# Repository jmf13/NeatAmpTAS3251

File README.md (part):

# NeatAmpTAS3251 — 2 × 170 W Class-D Amplifier with I²S Input, ESP32-S3 Control and DSP-Ready Design

> ⚠️ **Hobby project.** No deadlines, no warranties, no guarantees. Use at your own risk.

A stereo Class-D power amplifier built around the **Texas Instruments TAS3251**
(digital-input, 2 × 175 W into 4 Ω). It takes I²S audio directly, so there is no
analog input stage to add noise. An **ESP32-S3** configures and supervises the
amplifier over I²C (volume, EQ, faults, power sequencing), and the board is
prepared for an **ADAU1466 DSP**. A single 35 V supply feeds the power stage. Low-noise
buck + LDO rails derived from it supply everything else, and USB-C powers the digital side for
programming.

This README describes **V1.3**, the current design (KiCad 10, layout in progress).
It also explains how to bring the V1.0/V1.1 prototype boards as close to V1.3 as
possible.

---

## Contents

- [At a glance](#at-a-glance)
- [Project status](#project-status)
- [Documentation map](#documentation-map)
- [What's new in V1.3](#whats-new-in-v13)
- [Upgrading V1.0/V1.1 boards towards V1.3](#upgrading-v10v11-boards-towards-v13)
- [Building a V1.3 board](#building-a-v13-board)
- [Hardware description](#hardware-description)
  - [Power supply](#power-supply)
  - [Protection](#protection)
  - [TAS3251 amplifier](#tas3251-amplifier)
  - [ESP32-S3 controller](#esp32-s3-controller)
  - [I²S audio input](#i2s-audio-input)
- [Production details (JLCPCB)](#production-details-jlcpcb)
- [Design files and tools](#design-files-and-tools)
- [Revision history](#revision-history)
- [Next versions: ideas](#next-versions-ideas)
- [Original project and license](#original-project-and-license)

---

## At a glance

| | |
|---|---|
| Amplifier | TI TAS3251, stereo BTL, **2 × 175 W into 4 Ω** at 35 V, digital (I²S) input, built-in DSP |
| PWM frequency | 600 kHz (set by R38, selectable 600 / 500 / 450 kHz) |
| Output filter | 10 µH + 1.05 µF film caps per leg (f₀ ≈ 49 kHz). Footprints for MA5172-AE (THT; 7 µH MA5173-AE is the same family) and Coilcraft XGL1712 (SMD) |
| Supply | One external **35 V** supply (Mean Well UHP-500-36, trimmed). USB-C 5 V for the digital side only |
| Controller | ESP32-S3-WROOM-1U-N8R8 (Wi-Fi, 8 MB flash, 8 MB Octal PSRAM), firmware in [`tas/`](tas/README.md) |
| DSP | ADAU1466 ready: I²S connector, supply and I²C prepared |
| Protection | 5 A slow-blow fuse, reverse-polarity P-FET, 36 V TVS, pop-free power sequencing with PVDD monitoring |
| Cooling | ATS heatsink designed for TI's TAS3251EVM, bonded to board GND |
| PCB | 161.55 × 124.43 mm, 4 layers, 2 oz outer copper, JLCPCB assembled (top side) |
| Design tool | KiCad 10 (V1.3). EasyEDA Pro for V1.0–V1.2 |

<p align="center"><em>V1.2 PCB, top view (V1.3 renders will follow when the layout is finished)</em></p>

---

## Project status

| Version | Tool | State |
|---|---|---|
| V1.0 | EasyEDA Pro | 5 boards built (JLCPCB). Needs rework before use, see [Upgrading V1.0/V1.1](#upgrading-v10v11-boards-towards-v13) |
| V1.1 | EasyEDA Pro | USB-C orientation fix. Same rework as V1.0 otherwise |
| V1.2 | EasyEDA Pro | Layout done, DRC clean, **not produced**. Superseded by V1.3 |
| **V1.3** | **KiCad 10** | **Schematic done (ERC clean). PCB placement done, routing in progress.** Not yet produced |

**What's left before V1.3 can be ordered** is tracked in the review's
[open items summary](hw_review_2026-11-06.md#open-items):

- [pending actions](hw_review_2026-11-06.md#pending): routing, silkscreen, BOM, firmware, docs
- [parts to buy separately](hw_review_2026-11-06.md#purchase)
- [bottom-side parts](hw_review_2026-11-06.md#bottom-parts)
- [bench tests](hw_review_2026-11-06.md#hw-tests) for the first boards

⚠️ No revision has been validated in real operation yet. Treat the design as
experimental until the bench tests are done.

---

## Documentation map

| Document | What's in it |
|---|---|
| This README | Overview, V1.3 hardware description, building and upgrading boards |
| [hw_review_2026-11-06.md](hw_review_2026-11-06.md) | Full hardware review: every finding (P0 fixes, P1 savings, P2 improvements) with reasoning, datasheet references and status. Starts with the **open items summary** |
| [tas/README.md](tas/README.md) | ESP32-S3 firmware: ESP-IDF setup, build, debugging, firmware architecture, and the **step-by-step V1.0/V1.1 rework checklist** |
| [KiCADv10/README.md](KiCADv10/README.md) | How the KiCad 10 project was converted from EasyEDA, libraries and netlist checks |
| [Datasheets/](Datasheets/) | TAS3251, LMQ66430-Q1, TPS7A47, UHP-500, ADAU1462/1466, XU316-1024-QF60B (`C7397517.pdf`), heatsink datasheet and STEP |

---

## What's new in V1.3

V1.3 is the result of a full hardware review against the datasheets. The
most important changes are listed below. Each links to the detailed finding.

**Reliability and protection**

- **Reverse-polarity FET Q1 fixed.** It was mounted source-to-input on V1.0–V1.2, so it did not block a reversed supply. → [P0-6](hw_review_2026-11-06.md#p0-6)
- **F1 is now a slow-blow fuse** (0452005.MRL), sized for the 6600 µF PVDD inrush. → [P0-4](hw_review_2026-11-06.md#p0-4)
- **1 µF PVDD bypass caps right at the TAS3251 pins** (C108/C109, bottom side), as TI requires to keep output ringing below the 50 V maximum. → [V1.3-4](hw_review_2026-11-06.md#v13-4)
- **ESP32 EN pull-up** (R52 10 kΩ). EN used to float. → [P0-1](hw_review_2026-11-06.md#p0-1)
- **I²C moved off the ESP32 strapping pins** (SDA IO0 → IO47, SCL IO45 → IO21). A reset during an I²C transfer could leave the ESP32 in download mode. → [P0-2](hw_review_2026-11-06.md#p0-2)
- **C1 (feed-forward cap on the 13.2 V buck) removed.** At 10 nF it was ~50× over TI's limit. → [P0-5](hw_review_2026-11-06.md#p0-5)

**Pop-free switch-on and switch-off** → [P0-7](hw_review_2026-11-06.md#p0-7)
- RESET_AMP and ENABLE_12V are now **pulled down**: the power stage stays off until the firmware has configured it.
- **PVDD sense** divider on IO8 (R53/R54/C70): the firmware sees the supply collapse at mains-off and mutes before the power stage drops out.
- R55 10 kΩ in series with the TPS7A4701 EN pin protects it when 13.2 V is absent.

**Audio quality**

- DAC supply pins get 1 µF at the pin (C61/C67) instead of 100 nF. → [V1.3-4 #2](hw_review_2026-11-06.md#v13-4)
- DAC → SPK_IN network: 0.1 % thin-film resistors (R23–R30), C0G 1 nF, coupling caps C57–C60 moved next to the SPK_IN inputs, signal chain routed as differential pairs over a reworked AGND area. → [V1.3-4 #5](hw_review_2026-11-06.md#v13-4-f5), [P1-6](hw_review_2026-11-06.md#p1-6)
- Ferrite bead + 10 µF in front of the analog 3.3 V LDO (L15, C77). → [P2-1](hw_review_2026-11-06.md#p2-1)
- PWM frequency set by a single resistor (R38) close to the TAS3251 instead of a jumper header 35 mm away. → [V1.3-4 #6](hw_review_2026-11-06.md#v13-4-f6)

**Mechanical and PCB**

- **KiCad 10** project, 4-layer JLC04162H-7628 stack-up with **2 oz outer copper** and matching design rules. → [V1.3-3](hw_review_2026-11-06.md#v13-3)
- Board **6 mm wider**: the output stage moved to the new edge.
- **Proper heatsink** (ATS-TI1OP-1099-C1-R1, made for TI's TAS3251EVM), grounded through plated mounting holes. → [V1.3-1](hw_review_2026-11-06.md#v13-1)
- 3.3 V supply connector CN5: screw terminal → JST XH 2-pin. → [V1.3-2](hw_review_2026-11-06.md#v13-2)
- Test points reduced from 30 to 15, and all useful ones are reachable with the heatsink fitted. → [V1.3-5](hw_review_2026-11-06.md#v13-5)
- H2 expansion header reduced from 2×12 to 2×7 (now CN12).
- **All connectors renamed to CN** (V1.0–V1.2 silkscreen still shows the old names):

  | V1.0–V1.2 | V1.3 | Function |
  |---|---|---|
  | U7 | CN4 | Expansion, JST XH 6-pin |
  | U10 | CN7 | DSP control (I²C, reset, selfboot), JST XH 6-pin |
  | U11 | CN8 | I²S to/from DSP board, JST XH 6-pin |
  | U14 | CN9 | ESP32 ↔ TAS3251 control jumpers, 2×4 |
  | U15 | CN10 | Power-control jumpers, 2×4 |
  | H1 | CN11 | 4-pin header |
  | H2 | CN12 | Expansion header, 2×7 |
  | H3 | CN13 | Oscillator sync (OSC_IOM/IOP) + SDOUT, 4-pin |
  | USBC1 | CN14 | USB-C |
  | — | CN6 | New: DSP board power, JST XH 4-pin |

  Text describing V1.0/V1.1 boards (rework steps in `tas/README.md`) keeps the old names on purpose.

**BOM**

- Cheaper Basic parts where the specification allows, fewer unique parts (67 → 61 LCSC part numbers). → [P1](hw_review_2026-11-06.md#p1)
- CLIP LED is now yellow (it was the same colour as FAULT).

---

## Upgrading V1.0/V1.1 boards towards V1.3

The five V1.0/V1.1 prototypes are used for firmware development and first
listening tests. Most V1.3 fixes can be retrofitted by hand. The step-by-step
instructions (with checks after each step) are in the
[V1.0/V1.1 rework checklist](tas/README.md#hardware-v10v11-rework-checklist-before-first-power-up)
in the firmware README. This table summarises what to do and how important it is.

### Must do before the first power-up

| # | V1.3 change | What to do on V1.0/V1.1 | Steps |
|---|---|---|---|
| 1 | IO35–IO37 are reserved for the Octal PSRAM (fixed in V1.2) | Remove C51, R17, R18. Bodge the status LEDs to IO8/IO9. Don't press SW2 (or move it to IO10) | [A1–A5](tas/README.md#a-rework-soldering-iron-board-unpowered) |
| 2 | EN pull-up R52 | 10 kΩ from TP9 (EN) to 3.3 V | [A6](tas/README.md#a-rework-soldering-iron-board-unpowered) |
| 3 | C1 DNP on the 13.2 V buck | Remove C1 (10 nF). TP2 must then read 13.2 V | [A7](tas/README.md#a-rework-soldering-iron-board-unpowered) |
| 4 | Shunts on U14/U15/H2/U13 | Fit all control shunts. U13: **exactly one** pair, 3-4 = 10 kΩ = 600 kHz | [B](tas/README.md#b-shunts--jumpers) |

### Must do before running at full PVDD and high power

| # | V1.3 change | What to do on V1.0/V1.1 | Steps |
|---|---|---|---|
| 5 | 1 µF PVDD bypass at pins 35/40 (C108/C109) | Solder a 1 µF 100 V X7R from the PVDD copper nearest each pin to GND, shortest loop. **Never on the pin row** | [A8](tas/README.md#a-rework-soldering-iron-board-unpowered), [review](hw_review_2026-11-06.md#v10-pvdd) |

Until then, run at reduced PVDD (20–24 V) and low volume only.

### Recommended (makes the board behave like V1.3)

| # | V1.3 change | What to do on V1.0/V1.1 | Steps |
|---|---|---|---|
| 6 | RESET_AMP / ENABLE_12V default off | 4.7 kΩ U15-8 → GND; remove R45 and add 10 kΩ U14-6 → GND | [P1](tas/README.md#optional-pop-free-rework-v13-equivalent) |
| 7 | PVDD sense | 100 kΩ / 6.8 kΩ / 100 nF divider from TP1 to U7 pin 3 (**IO4** instead of IO8) | [P2](tas/README.md#optional-pop-free-rework-v13-equivalent) |
| 8 | F1 slow-blow | Replace F1 with 0452005.MRL (same footprint) | [P3](tas/README.md#optional-pop-free-rework-v13-equivalent) |
| 9 | SW2 user button on IO10 | Cut the trace to IO35, wire SW2 to IO10, add a 10 kΩ pull-up | [SW2 on IO10](tas/README.md#optional-sw2-on-io10-v12-equivalent) |

Without 6–8 the board works, but clicks at switch-on and thumps at switch-off.
Mute before switching off the mains ([P4](tas/README.md#optional-pop-free-rework-v13-equivalent)),
and power up from a current-limited supply rather than hot-plugging a stiff 36 V one.

### Optional (audio refinements, same footprints)

These are not in the firmware README's checklist yet. They are simple part swaps on
existing pads:

| # | V1.3 change | What to do on V1.0/V1.1 |
|---|---|---|
| 10 | 1 µF at DAC_DVDD / DAC_AVDD pins (C67/C61) | Replace the 100 nF caps at U12 pins 9 and 56 with 1 µF X7R ≥ 25 V of the same size |
| 11 | Thin-film DAC network | Replace R23–R26 (499 Ω) and R27–R30 (100 kΩ) with 0.1 % thin-film parts of the same size |
| 12 | R55 10 kΩ in series with U2 EN | Low priority. Only matters if 3.3 V is present without 13.2 V (USB-C powering) |

### Not possible on V1.0/V1.1: work around instead

| V1.3 change | Workaround on V1.0/V1.1 |
|---|---|
| Q1 reverse-polarity FET orientation | **Check CN1 polarity with a meter before every connection** ([step 12a](tas/README.md#d-first-36-v-power-up)) |
| USB-C (V1.0 only, rotated) | Flash over UART ([section C](tas/README.md#c-flash-the-firmware-first-without-36-v)). No JTAG debugging on V1.0 |
| I²C off IO0/IO45 | Stays on IO0/IO45. Harmless on the N8R8 module. If a warm reset leaves the board in download mode, power-cycle it |
| Pin map (LEDs, DSP pins, ADR) | V1.0/V1.1 boards keep the V1.2 firmware pin map. V1.3 needs the new map ([open item A17](hw_review_2026-11-06.md#pending)) |
| Grounded heatsink, wider board, 2 oz design rules, AGND rework, L15 ferrite, R38 next to FREQ_ADJ | Layout changes, not retrofittable |

The remaining differences between a reworked board and V1.2/V1.3 are listed in
[Reworked V1.0/V1.1 vs V1.2](tas/README.md#reworked-v10v11-vs-v12).

---

## Building a V1.3 board

### 1. Order

- **PCB + top-side assembly at JLCPCB.** Settings in [Production details](#production-details-jlcpcb).
  On the BOM page, set the bottom-side parts to **Do Not Place** (list below).
- **Separate LCSC order** for the bottom-side parts: JLCPCB doesn't ship loose parts with a PCBA order.
- **Mouser** (or similar): output inductors and the heatsink.
- Hardware: 2 × metal M3 screws for the heatsink, thermal paste (not an insulating pad).

The full purchase list with quantities and alternatives is in the review:
[components to purchase separately](hw_review_2026-11-06.md#purchase).

### 2. Hand-fit the parts JLCPCB doesn't place

| Part(s) | What | Source |
|---|---|---|
| C108, C109, C80, C81, C20, C68 | Bottom-side capacitors, see [Bottom-side parts](#bottom-side-parts-hand-soldered) | LCSC |
| L7–L14 | Output inductors: **one per leg**, either MA5172-AE (THT) or XGL1712-103MED (SMD) | Mouser |
| Heatsink | ATS-TI1OP-1099-C1-R1 with 2 × metal M3 screws from the bottom and thermal paste | Mouser / Digi-Key |
| R39/R40, R56 | DNP by default. Fit only for multi-board sync or target mode | LCSC |

### 3. Bring up and test

Follow the bring-up order in the review's
[HW tests and measurements](hw_review_2026-11-06.md#hw-tests):

1. **Before power:** bottom parts fitted, heatsink grounded, CN1 polarity checked.
2. **Digital side first:** power from USB-C (or 5 V on H2 pin 1) and flash the firmware.
3. **First PVDD:** current-limited bench supply at 20–24 V. Check all rails on the [test points](#test-points).
4. **Full 35 V:** inrush, PSU start-up, pop/click and output overshoot measurements.
5. **Audio:** THD+N, frequency response, inductor comparison.

---

## Hardware description

### Power supply

The supply is a multi-rail design. The noisy, high-current steps use 2.2 MHz bucks,
and the sensitive rails get an LDO after the buck.

```text
                 ┌─ U1 LMQ66430 buck ─→ +13.2V ─ FB ─→ U2 TPS7A4701 LDO ─→ 12V_GVDD (TAS3251 gate drive)
35 V PSU ─ F1 ─ Q1 ─→ PVDD ─┤
   (CN1)        (D2 TVS)    ├─ U3 LMQ66430 buck ─→ 5 V ─ D5 ─┐
                 │          │                                ├─→ +5V ─┬─ U4 AP63203 buck ─→ 3.3V (digital)
                 │   USB-C VBUS ─────────────────── D3 ──────┘        └─ L15 ─ U5 TPS7A2033 LDO ─→ +3.3VA (DAC analog)
                 └─→ TAS3251 PVDD (power stage), 3 × 2200 µF bulk
```

| Rail | Voltage | Source | Feeds |
|---|---|---|---|
| PVDD | 35 V | External PSU via F1, Q1 | TAS3251 output stage, both bucks |
| +13.2V | 13.2 V | U1 LMQ66430 buck | U2 LDO input (GOOD_13.2V = U1 power-good) |
| 12V_GVDD | 12.0 V | U2 TPS7A4701 LDO | TAS3251 GVDD_A/B. Enabled by the ESP32 (ENABLE_12V) |
| +5V (**≈ 4.6 V**) | 4.4–4.8 V | U3 buck 5.02 V (via D5) or USB-C (via D3) | 3.3 V buck, analog LDO, status LEDs, I²S connector |
| 3.3V | 3.3 V | U4 AP63203 buck | ESP32-S3, TAS3251 DAC_DVDD, ADAU1466 digital |
| +3.3VA | 3.3 V | U5 TPS7A2033 LDO | TAS3251 DAC_AVDD only |

#### External PVDD supply: Mean Well UHP-500-36

The recommended supply is the **Mean Well UHP-500-36**
([datasheet](Datasheets/UHP-500-spec.pdf)).

| Parameter | UHP-500-36 | Relevance to this board |
|---|---|---|
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
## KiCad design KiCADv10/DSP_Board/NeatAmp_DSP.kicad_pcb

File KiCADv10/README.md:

# NeatAmp MainBoard – KiCad schematic generated from EasyEDA Pro netlist

Source: `Netlist_Class_D_amp_2026-11-10.enet` (EasyEDA Pro, V1.2), 233 components, 138 nets.

## Status
- **Verified:** KiCad's exported netlist matches the EasyEDA netlist exactly (138/138 nets, identical pin sets; 31 NC pins = 31 no-connect flags).
- **Faithful 1:1 copy of V1.2.** The P0 fixes from `hw_review_2026-11-06.md` are **not** applied yet. Apply them as a separate commit.
- Written in KiCad 7 file format; KiCad 10 opens it and upgrades it on save.

## How it is drawn
- 5 sheets = original EasyEDA pages (page taken from each part's EasyEDA Channel ID).
- Every pin carries a label: **global labels** for named nets (cross-sheet), **local labels** `N<page>N<id>` for EasyEDA auto-nets (`$4N1568` → `N4N1568`).
- Parts are grouped around the IC they connect to (power nets ignored for grouping); pure decoupling parts sit in a separate group.
- Symbols are generic boxes generated from the real pin numbers/names (library `NeatAmp.kicad_sym`). Swap them for nicer symbols later with *Change Symbol*; pins match by number.
- Every symbol keeps its fields: Value, Footprint, LCSC, MPN, Manufacturer, JLC Class, Datasheet, Description, original EasyEDA footprint/device name. `in_bom` follows EasyEDA "Add into BOM" (test points excluded).

## Libraries
1. `pip install easyeda2kicad`
2. `./get_lcsc_libs.sh`: fetches symbol + footprint + 3D for all 67 LCSC numbers into `libs/easyeda2kicad.*`.
3. Footprint fields point to `easyeda2kicad:<EasyEDA footprint name>`. easyeda2kicad normally names footprints the same way. Any that differ show up as missing footprints in *Update PCB from Schematic*; fix them with *Tools → Edit Symbol Fields* (filter by the `EasyEDA Footprint` column).
4. Parts without LCSC number:
   - Test points → `TestPoint:TestPoint_Pad_D1.0mm` (KiCad standard)
   - L7/L9/L11/L13 (XGL1712, SMD) → `NeatAmp_custom:IND-SMD_L17.2-W18.2` (converted from the EasyEDA footprint in `EasyEDA-Pro/libraries/TAS3251Components.elib`; no 3D model yet) and L8/L10/L12/L14 (MA5172-AE, THT) → `NeatAmp_custom:MA5172AE` (vendor KiCad footprint + `NeatAmp_custom.3dshapes/MA5172-AE.stp`). Both footprints are intentional (alternative inductors to compare); only one per leg is mounted.

## Re-check after editing
```
kicad-cli sch export netlist --format kicadxml -o new.xml NeatAmp.kicad_sch
python3 tools/cmp.py Netlist_Class_D_amp_2026-11-10.enet new.xml
```
(Expect differences only where you deliberately changed the circuit.)

## Regenerate
`python3 tools/gen.py <netlist.enet> <outdir> NeatAmp`

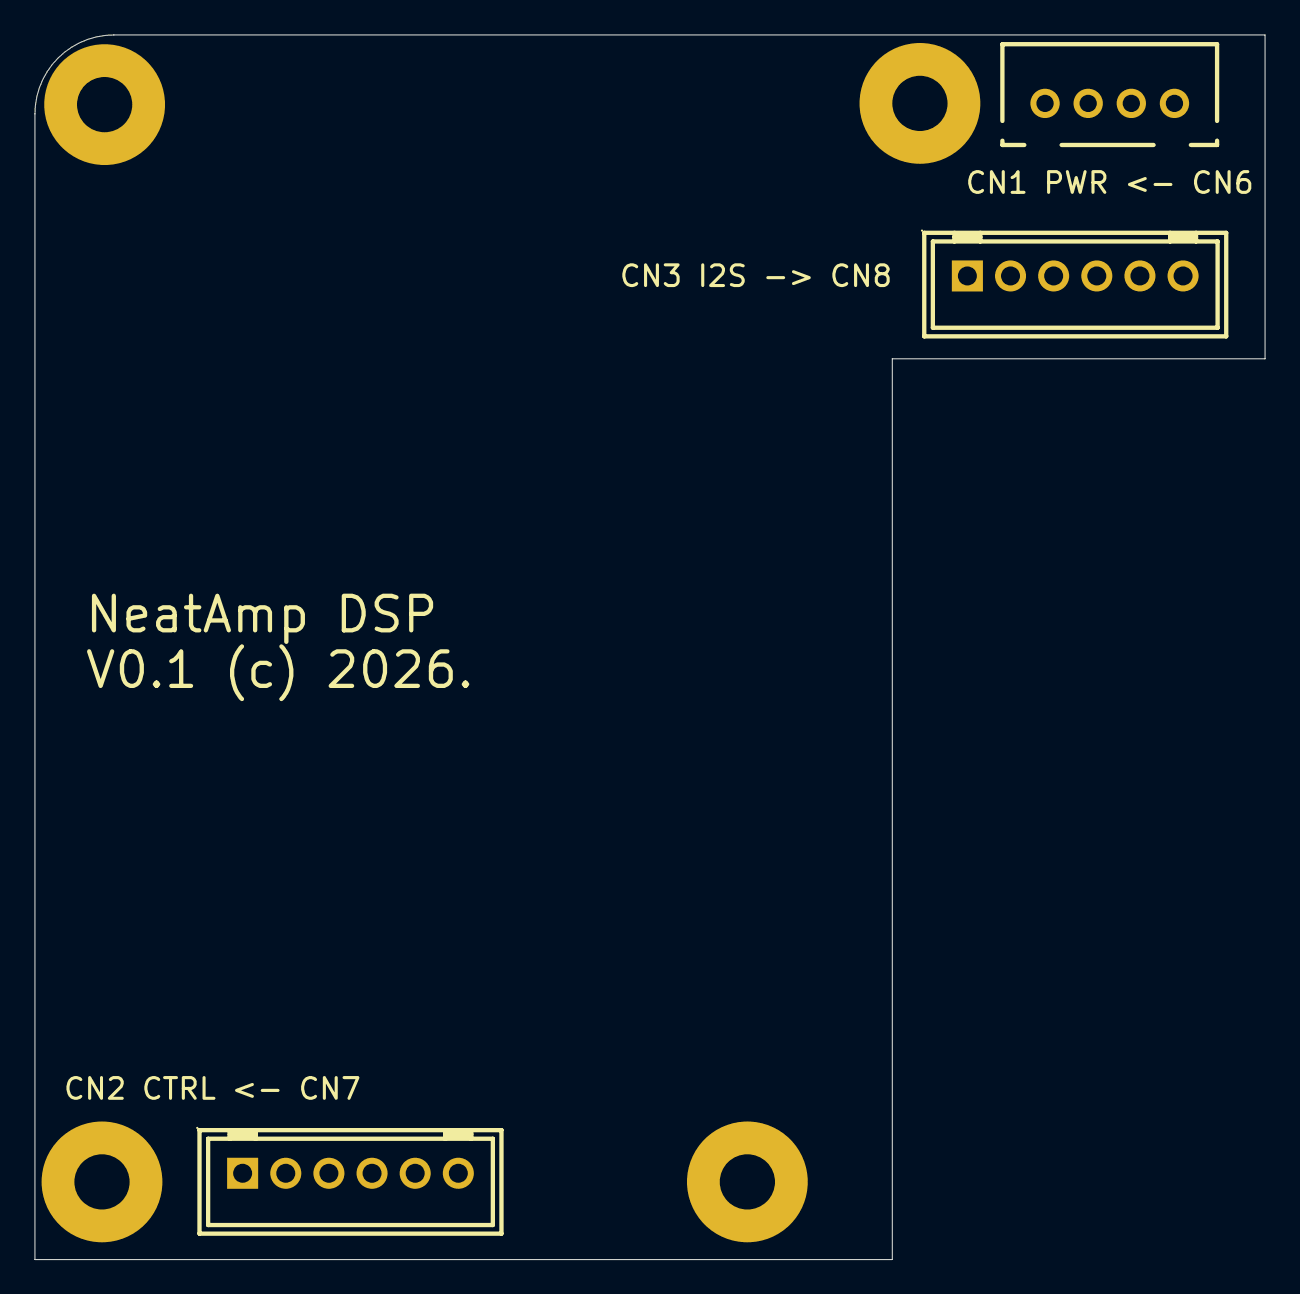
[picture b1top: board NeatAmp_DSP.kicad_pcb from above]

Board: 4 copper layers, 71.3 x 71.0 mm, 7 parts (0 on the bottom side), 2 nets, no tracks yet.

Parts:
CN1: B4B-XH-A(LF)(SN); CONN-TH_B4B-XH-A-LF-SN
CN2, CN3: B6B-XH-A(LF)(SN); CONN-TH_6P-P2.50_B6B-XH-A-LF-SN
MH1, MH2, MH3, MH4: M3; MountingHole_3.2mm_M3_Pad_7mm

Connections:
/+5V_IN: CN1.1, CN1.2
/GND: CN1.3, CN1.4, CN2.1, CN3.1

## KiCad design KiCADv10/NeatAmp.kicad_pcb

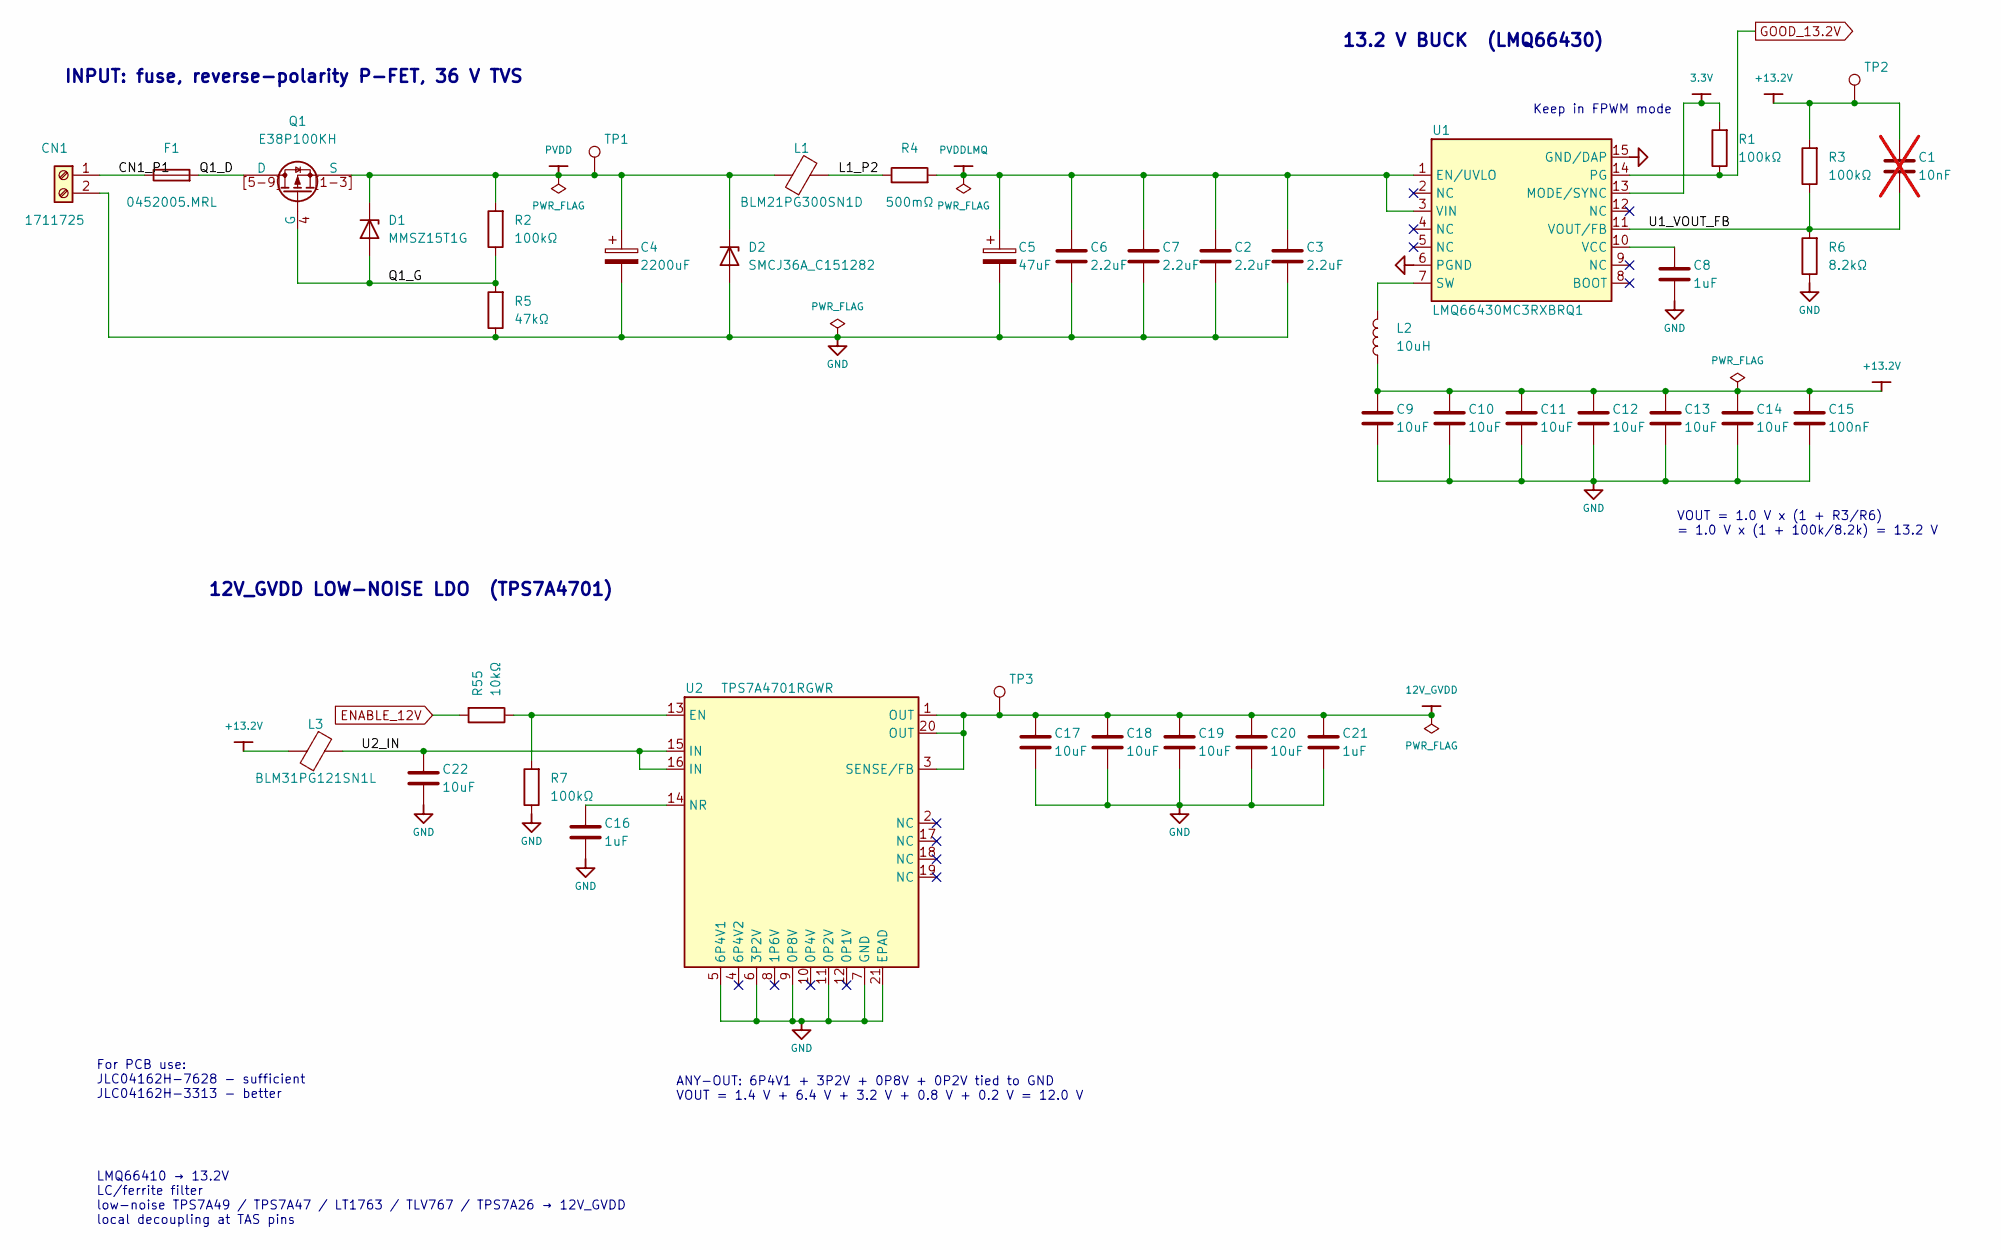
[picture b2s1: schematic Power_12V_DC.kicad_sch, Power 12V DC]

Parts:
C1: 10nF; C0402; MPN FCC0402B103K500AT; LCSC C5137480; not fitted
C2, C3, C6, C7: 2.2uF; C1206; MPN CL31B225KCHSNNE; LCSC C170101
C4: 2200uF; CAP-TH_BD18.0-P7.5-D0.8-FD; MPN NXA 63V 2200UF 18*40; LCSC C2827938
C5: 47uF; CAP-SMD_BD6.3-L6.6-W6.6-LS7.2-FD; MPN VZH470M1HTR-0607L; LCSC C2902971
C8: 1uF; C1206; MPN CL31B105KCHNNNE; LCSC C13832
C9, C10, C11, C12, C13, C14, C17, C18, C19, C20, C22: 10uF; C1210; MPN CL32B106KBJNNNE; LCSC C138687
C15: 100nF; C0402; MPN CL05B104KB54PNC; LCSC C307331
C16, C21: 1uF; C0603; MPN CL10B105KB8NQNC; LCSC C5199872
CN1: 1711725; CONN-TH_MKDS3-2-5.08; MPN 1711725; LCSC C89120
D1: MMSZ15T1G; SOD-123_L2.7-W1.6-LS3.7-RD; MPN MMSZ15T1G; LCSC C27754
D2: SMCJ36A_C151282; SMC_L7.1-W6.2-LS8.1-RD; MPN SMCJ36A; LCSC C151282
F1: 0452005.MRL; FUSE-SMD_L6.1-W2.6; MPN 0452005.MRL; LCSC C66503
L1: BLM21PG300SN1D; L0805; MPN BLM21PG300SN1D; LCSC C16903
L2: 10uH; IND-SMD_L7.1-W6.6; MPN SLO0630H100MTT; LCSC C207842
L3: BLM31PG121SN1L; L1206; MPN BLM31PG121SN1L; LCSC C85841
Q1: E38P100KH; DFN-8_L6.0-W5.0-P1.27-LS6.2-BL_VBQA2309; MPN E38P100KH; LCSC C29781155
R1, R2, R3, R7: 100kΩ; R0603; MPN 0603WAF1003T5E; LCSC C25803
R4: 500mΩ; R2512; MPN 25121WF500LT4E; LCSC C27777
R5: 47kΩ; R0603; MPN 0603WAF4702T5E; LCSC C25819
R6: 8.2kΩ; R0603; MPN FRC0603F8201TS; LCSC C2907069
R55: 10kΩ; R0603; MPN 0603WAF1002T5E; LCSC C25804
TP1, TP2, TP3: Test-Point; TestPoint_Pad_D1.0mm
U1: LMQ66430MC3RXBRQ1; VQFN-14_L2.6-W2.6-P0.50-BL; MPN LMQ66430MC3RXBRQ1; LCSC C19271903
U2: TPS7A4701RGWR; VQFN-20_L5.0-W5.0-P0.65-TL-EP; MPN TPS7A4701RGWR; LCSC C90084

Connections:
3.3V: R1.2, U1.13 (MODE/SYNC); also elsewhere on the board
12V_GVDD: C17.1, C18.1, C19.1, C20.1, C21.1, TP3.1 (1_1), U2.1 (OUT), U2.3 (SENSE/FB), U2.20 (OUT); also elsewhere on the board
+13.2V: C1.2, C9.1, C10.1, C11.1, C12.1, C13.1, C14.1, C15.2, L2.1, L3.2, R3.2, TP2.1 (1_1)
/Power 12V DC/CN1_P1: CN1.1, F1.1
/Power 12V DC/L1_P2: L1.2, R4.1
/Power 12V DC/Q1_D: F1.2, Q1.5 (D), Q1.6 (D), Q1.7 (D), Q1.8 (D), Q1.9 (D), Q1.[5-9] (D)
/Power 12V DC/Q1_G: D1.2 (A), Q1.4 (G), R2.1, R5.2
/Power 12V DC/U1_VOUT_FB: C1.1, R3.1, R6.2, U1.11 (VOUT/FB)
/Power 12V DC/U2_IN: C22.1, L3.1, U2.15 (IN), U2.16 (IN)
ENABLE_12V: R55.2; also elsewhere on the board
GND: C2.1, C3.1, C4.2, C5.2, C6.1, C7.1, C8.2, C9.2, C10.2, C11.2, C12.2, C13.2, C14.2, C15.1, C16.2, C17.2, C18.2, C19.2, C20.2, C21.2, C22.2, CN1.2, D2.2 (A), R5.1, R6.1, R7.1, U1.6 (PGND), U1.15 (GND/DAP), U2.5 (6P4V1), U2.6 (3P2V), U2.7 (GND), U2.9 (0P8V), U2.11 (0P2V), U2.21 (EPAD); also elsewhere on the board
GOOD_13.2V: R1.1, U1.14 (PG); also elsewhere on the board
unnamed: L2.2, U1.7 (SW)
unnamed: C8.1, U1.10 (VCC)
unnamed: R7.2, R55.1, U2.13 (EN)
unnamed: C16.1, U2.14 (NR)
PVDD: C4.1, D1.1 (K), D2.1 (K), L1.1, Q1.1 (S), Q1.2 (S), Q1.3 (S), Q1.[1-3] (S), R2.2, TP1.1 (1_1); also elsewhere on the board
PVDDLMQ: C2.2, C3.2, C5.1, C6.2, C7.2, R4.2, U1.1 (EN/UVLO), U1.3 (VIN); also elsewhere on the board

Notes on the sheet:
VOUT = 1.0 V x (1 + R3/R6) = 1.0 V x (1 + 100k/8.2k) = 13.2 V
12V_GVDD LOW-NOISE LDO (TPS7A4701)
INPUT: fuse, reverse-polarity P-FET, 36 V TVS
LMQ66410 → 13.2V LC/ferrite filter low-noise TPS7A49 / TPS7A47 / LT1763 / TLV767 / TPS7A26 → 12V_GVDD local decoupling at TAS pins
ANY-OUT: 6P4V1 + 3P2V + 0P8V + 0P2V tied to GND VOUT = 1.4 V + 6.4 V + 3.2 V + 0.8 V + 0.2 V = 12.0 V
For PCB use: JLC04162H-7628 - sufficient JLC04162H-3313 - better
13.2 V BUCK (LMQ66430)
Keep in FPWM mode

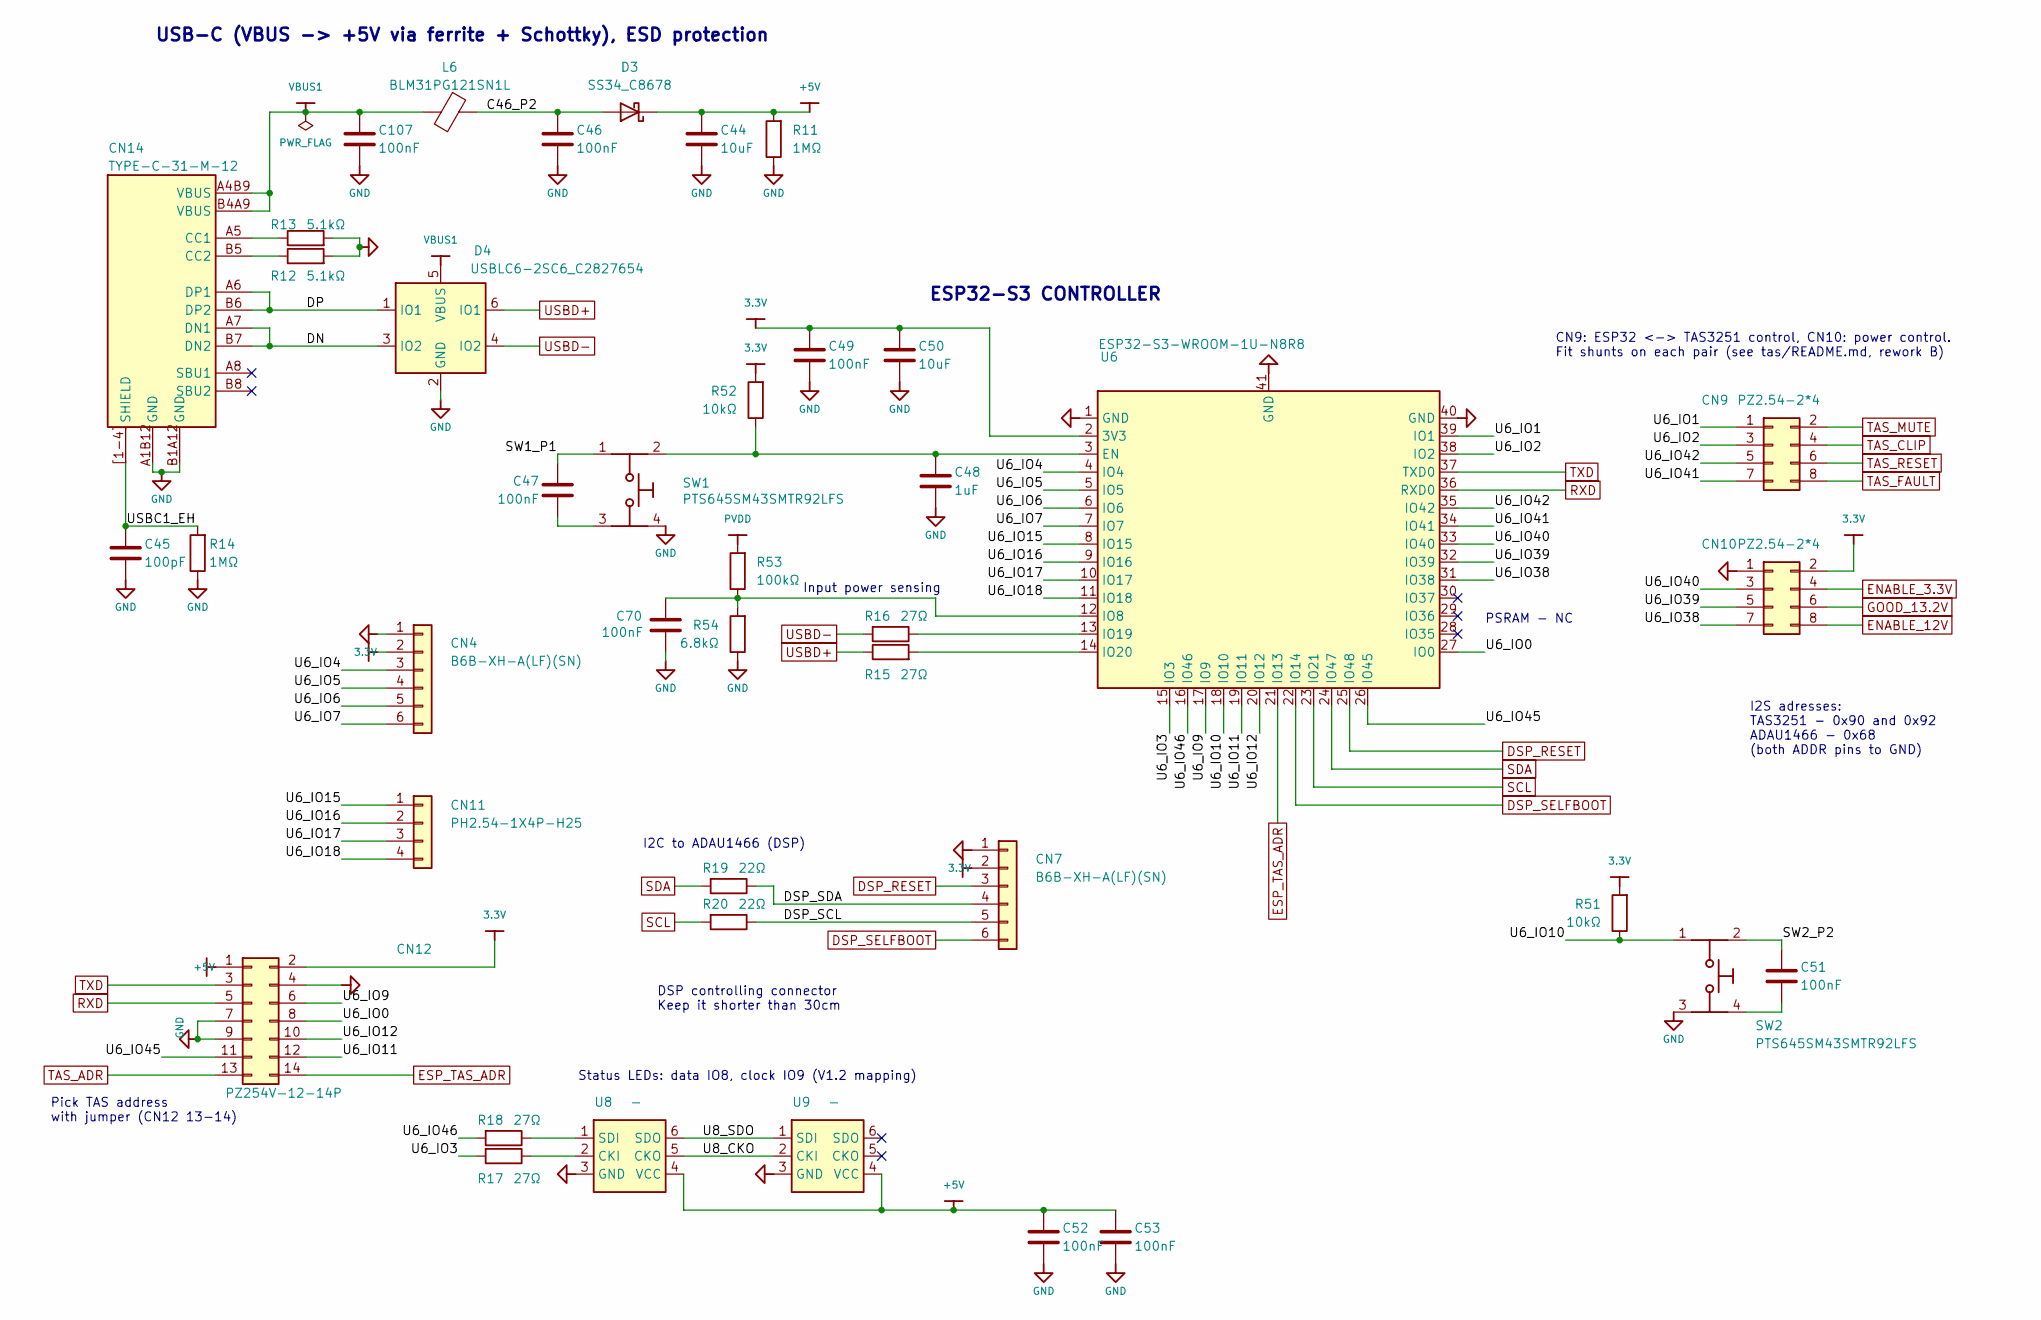
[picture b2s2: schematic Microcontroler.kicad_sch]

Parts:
C44, C50: 10uF; C1210; MPN CL32B106KBJNNNE; LCSC C138687
C45: 100pF; C0402; MPN 0402CG101J500NT; LCSC C1546
C46, C47, C49, C51, C52, C53, C70, C107: 100nF; C0402; MPN CL05B104KB54PNC; LCSC C307331
C48: 1uF; C0603; MPN CL10B105KB8NQNC; LCSC C5199872
CN4, CN7: B6B-XH-A(LF)(SN); CONN-TH_6P-P2.50_B6B-XH-A-LF-SN; MPN B6B-XH-A(LF)(SN); LCSC C144397
CN9, CN10: PZ2.54-2*4; HDR-TH_8P-P2.54-V-M-R2-C4-S2.54; MPN PZ2.54-2*4; LCSC C5156676
CN11: PH2.54-1X4P-H25; HDR-TH_4P-P2.54-V-M; MPN PH2.54-1X4P-H25; LCSC C42431808
CN12: PZ254V-12-14P; PinHeader_2x07_P2.54mm_Vertical; MPN PZ254V-12-14P; LCSC C492424
CN14: TYPE-C-31-M-12; USB-C_SMD-TYPE-C-31-M-12_1; MPN TYPE-C-31-M-12; LCSC C165948
D3: SS34_C8678; SMA_L4.3-W2.6-LS5.2-RD; MPN SS34; LCSC C8678
D4: USBLC6-2SC6_C2827654; SOT-23-6_L2.9-W1.6-P0.95-LS2.8-BL; MPN USBLC6-2SC6; LCSC C2827654
L6: BLM31PG121SN1L; L1206; MPN BLM31PG121SN1L; LCSC C85841
R11, R14: 1MΩ; R0603; MPN 0603WAF1004T5E; LCSC C22935
R12, R13: 5.1kΩ; R0603; MPN 0603WAF5101T5E; LCSC C23186
R15, R16, R17, R18: 27Ω; R0402; MPN 0402WGF270JTCE; LCSC C25100
R19, R20: 22Ω; R0402; MPN 0402WGF220JTCE; LCSC C25092
R51, R52: 10kΩ; R0603; MPN 0603WAF1002T5E; LCSC C25804
R53: 100kΩ; R0603; MPN 0603WAF1003T5E; LCSC C25803
R54: 6.8kΩ; R0603; MPN 0603WAF6801T5E; LCSC C23212
SW1, SW2: PTS645SM43SMTR92LFS; KEY-SMD_4P-L6.0-W6.0-P4.50-LS9.0; MPN PTS645SM43SMTR92LFS; LCSC C221880
U6: ESP32-S3-WROOM-1U-N8R8; WIRELM-SMD_ESP32-S3-WROOM-1U; MPN ESP32-S3-WROOM-1U-N8R8; LCSC C2980300
U8, U9: -; SMD_6P-L5.0-W5.0-TL; MPN SK9822; LCSC C2829089

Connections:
3.3V: C49.2, C50.1, CN4.2, CN7.2, CN10.2, CN12.2, R51.2, R52.2, U6.2 (3V3); also elsewhere on the board
+5V: C44.1, C52.1, C53.1, CN12.1, D3.2 (K), R11.2, U8.4 (VCC), U9.4 (VCC); also elsewhere on the board
/Microcontroler/C46_P2: C46.2, D3.1 (A), L6.1
/Microcontroler/DN: CN14.A7 (DN1), CN14.B7 (DN2), D4.3 (IO2)
/Microcontroler/DP: CN14.A6 (DP1), CN14.B6 (DP2), D4.1 (IO1)
/Microcontroler/DSP_SCL: CN7.5, R20.1
/Microcontroler/DSP_SDA: CN7.4, R19.1
/Microcontroler/SW1_P1: C47.2, SW1.1
/Microcontroler/SW2_P2: C51.2, SW2.2
/Microcontroler/U6_IO0: CN12.8, U6.27 (IO0)
/Microcontroler/U6_IO1: CN9.1, U6.39 (IO1)
/Microcontroler/U6_IO2: CN9.3, U6.38 (IO2)
/Microcontroler/U6_IO3: R17.2, U6.15 (IO3)
/Microcontroler/U6_IO4: CN4.3, U6.4 (IO4)
/Microcontroler/U6_IO5: CN4.4, U6.5 (IO5)
/Microcontroler/U6_IO6: CN4.5, U6.6 (IO6)
/Microcontroler/U6_IO7: CN4.6, U6.7 (IO7)
/Microcontroler/U6_IO9: CN12.6, U6.17 (IO9)
/Microcontroler/U6_IO10: R51.1, SW2.1, U6.18 (IO10)
/Microcontroler/U6_IO11: CN12.12, U6.19 (IO11)
/Microcontroler/U6_IO12: CN12.10, U6.20 (IO12)
/Microcontroler/U6_IO15: CN11.1, U6.8 (IO15)
/Microcontroler/U6_IO16: CN11.2, U6.9 (IO16)
/Microcontroler/U6_IO17: CN11.3, U6.10 (IO17)
/Microcontroler/U6_IO18: CN11.4, U6.11 (IO18)
/Microcontroler/U6_IO38: CN10.7, U6.31 (IO38)
/Microcontroler/U6_IO39: CN10.5, U6.32 (IO39)
/Microcontroler/U6_IO40: CN10.3, U6.33 (IO40)
/Microcontroler/U6_IO41: CN9.7, U6.34 (IO41)
/Microcontroler/U6_IO42: CN9.5, U6.35 (IO42)
/Microcontroler/U6_IO45: CN12.11, U6.26 (IO45)
/Microcontroler/U6_IO46: R18.2, U6.16 (IO46)
/Microcontroler/U8_CKO: U8.5 (CKO), U9.2 (CKI)
/Microcontroler/U8_SDO: U8.6 (SDO), U9.1 (SDI)
/Microcontroler/USBC1_EH: C45.2, CN14.1 (SHIELD), CN14.2 (SHIELD), CN14.3 (SHIELD), CN14.4 (SHIELD), CN14.[1-4] (SHIELD), R14.2
DSP_RESET: CN7.3, U6.25 (IO48)
DSP_SELFBOOT: CN7.6, U6.22 (IO14)
ENABLE_3.3V: CN10.4; also elsewhere on the board
ENABLE_12V: CN10.8; also elsewhere on the board
ESP_TAS_ADR: CN12.14, U6.21 (IO13)
GND: C44.2, C45.1, C46.1, C48.1, C49.1, C50.2, C52.2, C53.2, C70.1, C107.1, CN4.1, CN7.1, CN10.1, CN12.4, CN12.7, CN12.9, CN14.A1B12 (GND), CN14.B1A12 (GND), D4.2 (GND), R11.1, R12.2, R13.2, R14.1, R54.1, SW1.4, SW2.3, U6.1 (GND), U6.40 (GND), U6.41 (GND), U8.3 (GND), U9.3 (GND); also elsewhere on the board
GOOD_13.2V: CN10.6; also elsewhere on the board
unnamed: C47.1, SW1.3
unnamed: C51.1, SW2.4
unnamed: CN14.A5 (CC1), R13.1
unnamed: CN14.B5 (CC2), R12.1
unnamed: C48.2, R52.1, SW1.2, U6.3 (EN)
unnamed: C70.2, R53.1, R54.2, U6.12 (IO8)
unnamed: R16.1, U6.13 (IO19)
unnamed: R15.2, U6.14 (IO20)
unnamed: R17.1, U8.2 (CKI)
unnamed: R18.1, U8.1 (SDI)
PVDD: R53.2; also elsewhere on the board
RXD: CN12.5, U6.36 (RXD0)
SCL: R20.2, U6.23 (IO21); also elsewhere on the board
SDA: R19.2, U6.24 (IO47); also elsewhere on the board
TAS_ADR: CN12.13; also elsewhere on the board
TAS_CLIP: CN9.4; also elsewhere on the board
TAS_FAULT: CN9.8; also elsewhere on the board
TAS_MUTE: CN9.2; also elsewhere on the board
TAS_RESET: CN9.6; also elsewhere on the board
TXD: CN12.3, U6.37 (TXD0)
USBD+: D4.6 (IO1), R15.1
USBD-: D4.4 (IO2), R16.2
VBUS1: C107.2, CN14.A4B9 (VBUS), CN14.B4A9 (VBUS), D4.5 (VBUS), L6.2

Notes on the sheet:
Status LEDs: data IO8, clock IO9 (V1.2 mapping)
Pick TAS address with jumper (CN12 13-14)
USB-C (VBUS -> +5V via ferrite + Schottky), ESD protection
I2C to ADAU1466 (DSP)
I2S adresses: TAS3251 - 0x90 and 0x92 ADAU1466 - 0x68 (both ADDR pins to GND)
Input power sensing
CN9: ESP32 <-> TAS3251 control, CN10: power control. Fit shunts on each pair (see tas/README.md, rework B)
ESP32-S3 CONTROLLER
PSRAM - NC
DSP controlling connector Keep it shorter than 30cm

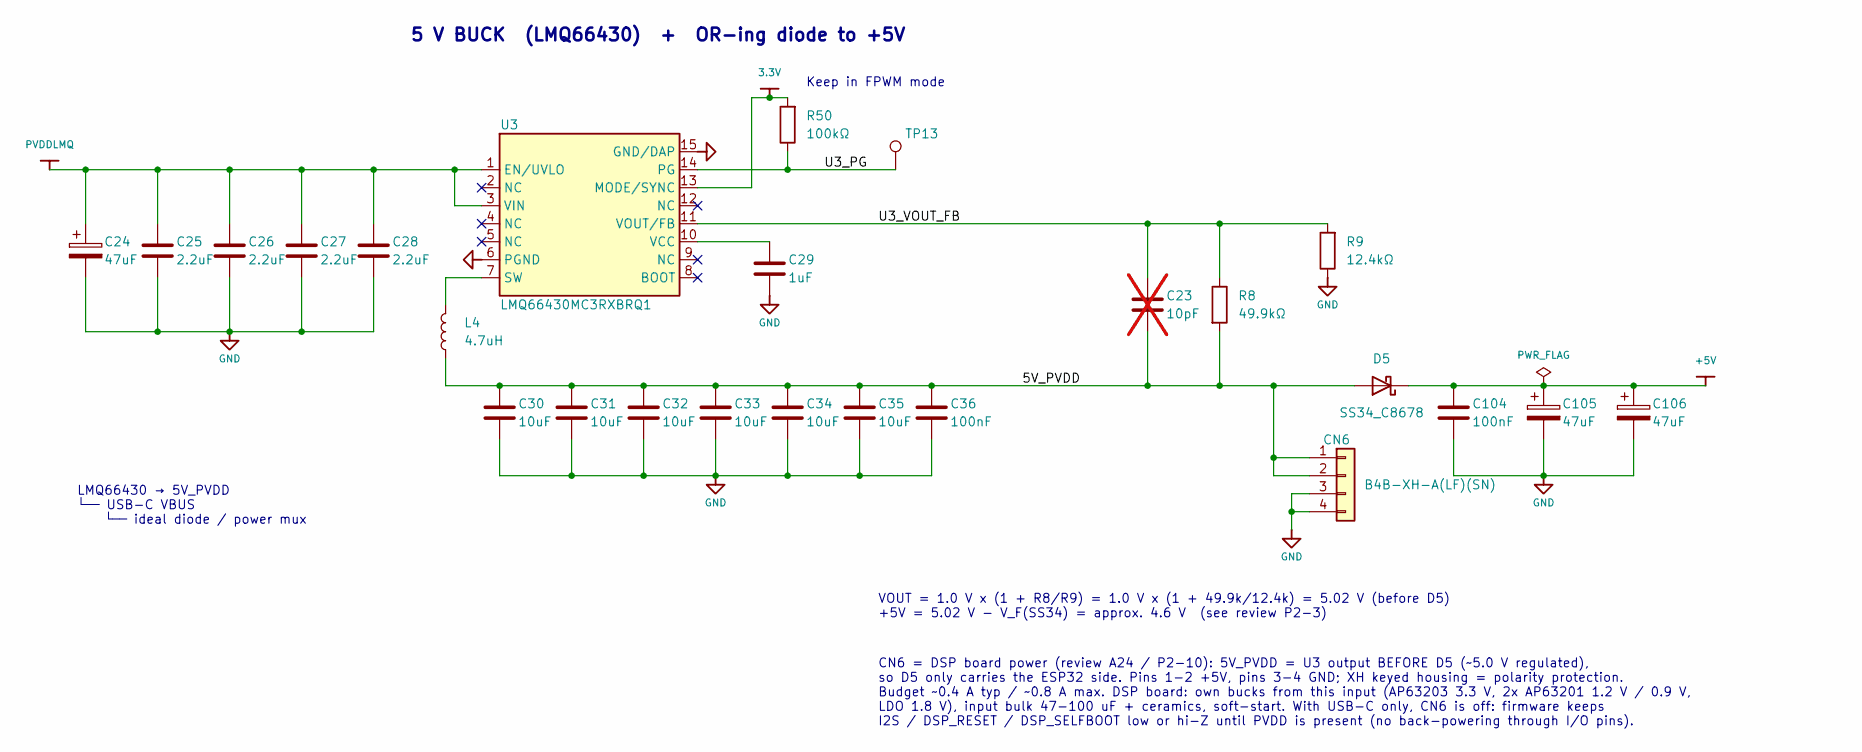
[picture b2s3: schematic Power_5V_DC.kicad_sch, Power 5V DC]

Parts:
C23: 10pF; C0402; MPN 04025A100JAT2A; LCSC C513314; not fitted
C24, C105, C106: 47uF; CAP-SMD_BD6.3-L6.6-W6.6-LS7.2-FD; MPN VZH470M1HTR-0607L; LCSC C2902971
C25, C26, C27, C28: 2.2uF; C1206; MPN CL31B225KCHSNNE; LCSC C170101
C29: 1uF; C1206; MPN CL31B105KCHNNNE; LCSC C13832
C30, C31, C32, C33, C34, C35: 10uF; C1210; MPN CL32B106KBJNNNE; LCSC C138687
C36, C104: 100nF; C0402; MPN CL05B104KB54PNC; LCSC C307331
CN6: B4B-XH-A(LF)(SN); CONN-TH_B4B-XH-A-LF-SN; MPN B4B-XH-A(LF)(SN); LCSC C144395
D5: SS34_C8678; SMA_L4.3-W2.6-LS5.2-RD; MPN SS34; LCSC C8678
L4: 4.7uH; IND-SMD_L10.2-W10.0; MPN YPRH105R-4R7M; LCSC C718262
R8: 49.9kΩ; R0603; MPN 0603WAF4992T5E; LCSC C23184
R9: 12.4kΩ; R0603; MPN 0603WAF1242T5E; LCSC C22865
R50: 100kΩ; R0603; MPN 0603WAF1003T5E; LCSC C25803
TP13: Test-Point; TestPoint_Pad_D1.0mm
U3: LMQ66430MC3RXBRQ1; VQFN-14_L2.6-W2.6-P0.50-BL; MPN LMQ66430MC3RXBRQ1; LCSC C19271903

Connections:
3.3V: R50.2, U3.13 (MODE/SYNC); also elsewhere on the board
+5V: C104.2, C105.1, C106.1, D5.2 (K); also elsewhere on the board
/Power 5V DC/5V_PVDD: C23.2, C30.1, C31.1, C32.1, C33.1, C34.1, C35.1, C36.2, CN6.1, CN6.2, D5.1 (A), L4.1, R8.2
/Power 5V DC/U3_PG: R50.1, TP13.1 (1_1), U3.14 (PG)
/Power 5V DC/U3_VOUT_FB: C23.1, R8.1, R9.2, U3.11 (VOUT/FB)
GND: C24.2, C25.1, C26.1, C27.1, C28.1, C29.2, C30.2, C31.2, C32.2, C33.2, C34.2, C35.2, C36.1, C104.1, C105.2, C106.2, CN6.3, CN6.4, R9.1, U3.6 (PGND), U3.15 (GND/DAP); also elsewhere on the board
unnamed: L4.2, U3.7 (SW)
unnamed: C29.1, U3.10 (VCC)
PVDDLMQ: C24.1, C25.2, C26.2, C27.2, C28.2, U3.1 (EN/UVLO), U3.3 (VIN); also elsewhere on the board

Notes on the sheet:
VOUT = 1.0 V x (1 + R8/R9) = 1.0 V x (1 + 49.9k/12.4k) = 5.02 V (before D5) +5V = 5.02 V - V_F(SS34) = approx. 4.6 V (see review P2-3)
LMQ66430 → 5V_PVDD └── USB-C VBUS └── ideal diode / power mux
Keep in FPWM mode
5 V BUCK (LMQ66430) + OR-ing diode to +5V
CN6 = DSP board power (review A24 / P2-10): 5V_PVDD = U3 output BEFORE D5 (~5.0 V regulated), so D5 only carries the ESP32 side. Pins 1-2 +5V, pins 3-4 GND; XH keyed housing = polarity protection. Budget ~0.4 A typ / ~0.8 A max. DSP board: own bucks from this input (AP63203 3.3 V, 2x AP63201 1.2 V 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

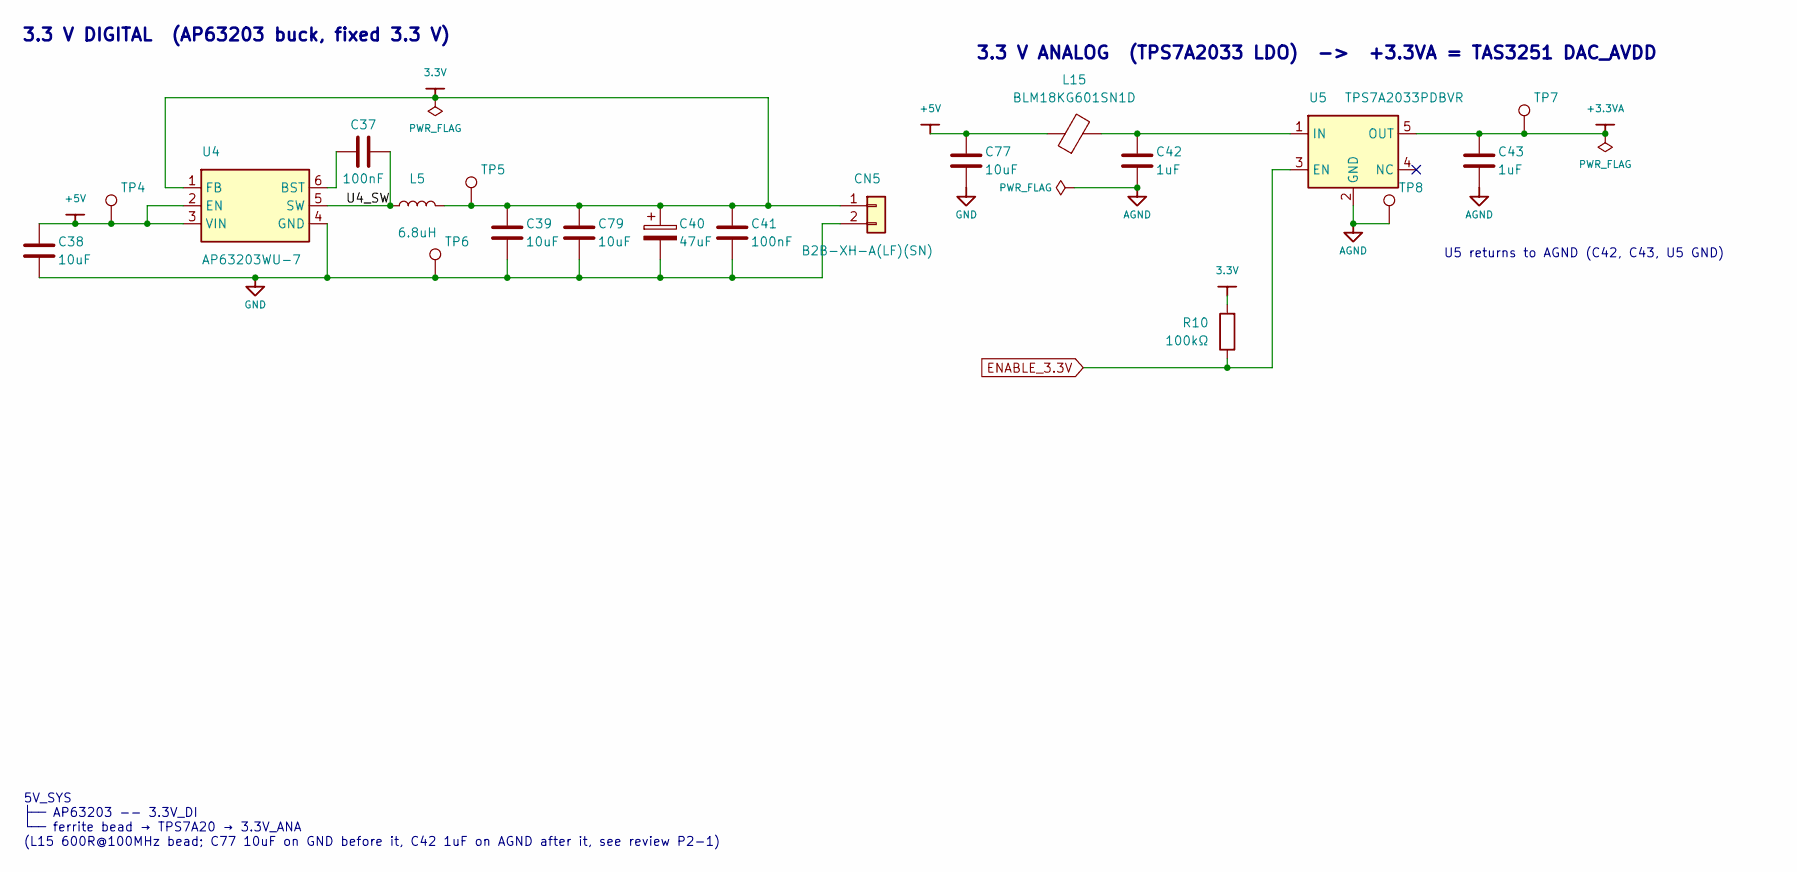
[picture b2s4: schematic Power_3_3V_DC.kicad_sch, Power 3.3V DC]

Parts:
C37, C41: 100nF; C0402; MPN CL05B104KB54PNC; LCSC C307331
C38, C39, C77, C79: 10uF; C1210; MPN CL32B106KBJNNNE; LCSC C138687
C40: 47uF; CAP-SMD_BD6.3-L6.6-W6.6-LS7.2-FD; MPN VZH470M1HTR-0607L; LCSC C2902971
C42, C43: 1uF; C0603; MPN CL10B105KB8NQNC; LCSC C5199872
CN5: B2B-XH-A(LF)(SN); CONN-TH_B2B-XH-A-LF-SN; MPN B2B-XH-A(LF)(SN); LCSC C158012
L5: 6.8uH; IND-SMD_L7.1-W6.6; MPN SLO0630H6R8MTT; LCSC C207841
L15: BLM18KG601SN1D; L0603; MPN BLM18KG601SN1D; LCSC C85833
R10: 100kΩ; R0603; MPN 0603WAF1003T5E; LCSC C25803
TP4, TP5, TP6, TP7, TP8: Test-Point; TestPoint_Pad_D1.0mm
U4: AP63203WU-7; TSOT-26_L2.9-W1.6-P0.95-LS2.8-BL; MPN AP63203WU-7; LCSC C780769
U5: TPS7A2033PDBVR; SOT-23-5_L2.9-W1.6-P0.95-LS2.8-BR; MPN TPS7A2033PDBVR; LCSC C2862740

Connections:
3.3V: C39.1, C40.1, C41.2, C79.1, CN5.1, L5.2, R10.2, TP5.1 (1_1), U4.1 (FB); also elsewhere on the board
+3.3VA: C43.1, TP7.1 (1_1), U5.5 (OUT); also elsewhere on the board
+5V: C38.1, C77.1, L15.1, TP4.1 (1_1), U4.2 (EN), U4.3 (VIN); also elsewhere on the board
/Power 3.3V DC/U4_SW: C37.2, L5.1, U4.5 (SW)
AGND: C42.2, C43.2, TP8.1 (1_1), U5.2 (GND); also elsewhere on the board
ENABLE_3.3V: R10.1, U5.3 (EN); also elsewhere on the board
GND: C38.2, C39.2, C40.2, C41.1, C77.2, C79.2, CN5.2, TP6.1 (1_1), U4.4 (GND); also elsewhere on the board
unnamed: C37.1, U4.6 (BST)
unnamed: C42.1, L15.2, U5.1 (IN)

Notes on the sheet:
5V_SYS ├── AP63203 -- 3.3V_DI └── ferrite bead → TPS7A20 → 3.3V_ANA (L15 600R@100MHz bead; C77 10uF on GND before it, C42 1uF on AGND after it, see review P2-1)
U5 returns to AGND (C42, C43, U5 GND)
3.3 V ANALOG (TPS7A2033 LDO) -> +3.3VA = TAS3251 DAC_AVDD
3.3 V DIGITAL (AP63203 buck, fixed 3.3 V)

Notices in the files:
README.md:
Original project and license:
- Based on [jmf13/NeatAmpTAS3251](https://github.com/jmf13/NeatAmpTAS3251/tree/master).
This project extends it with the ESP32-S3 controller, a redesigned power supply,
DSP preparation and the inductor comparison.
- License: [CC BY-SA 4.0](https://creativecommons.org/licenses/by-sa/4.0/), inherited from the original.
KiCADv10/DSP_Board/NeatAmp_DSP.kicad_pcb:
V0.1 (c) 2026.
KiCADv10/NeatAmp.kicad_pcb:
V 1.3 (c) 2026.
